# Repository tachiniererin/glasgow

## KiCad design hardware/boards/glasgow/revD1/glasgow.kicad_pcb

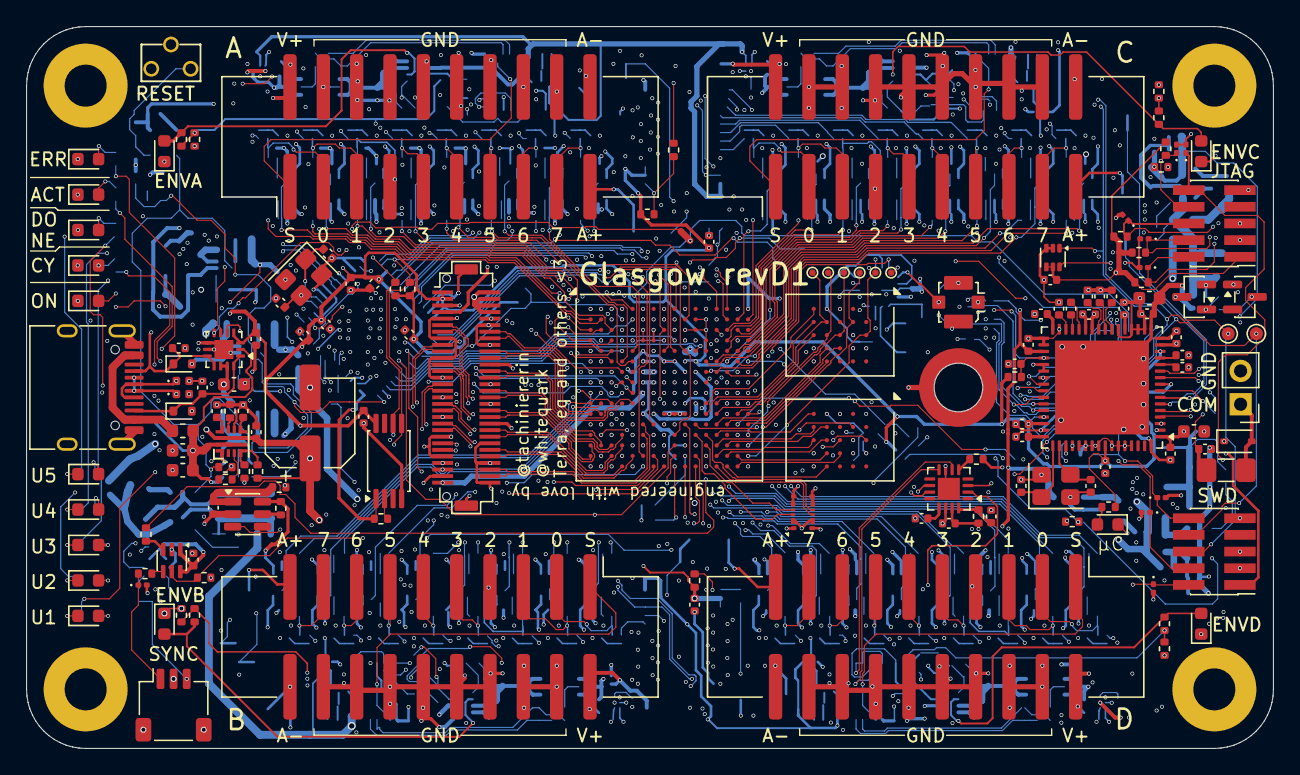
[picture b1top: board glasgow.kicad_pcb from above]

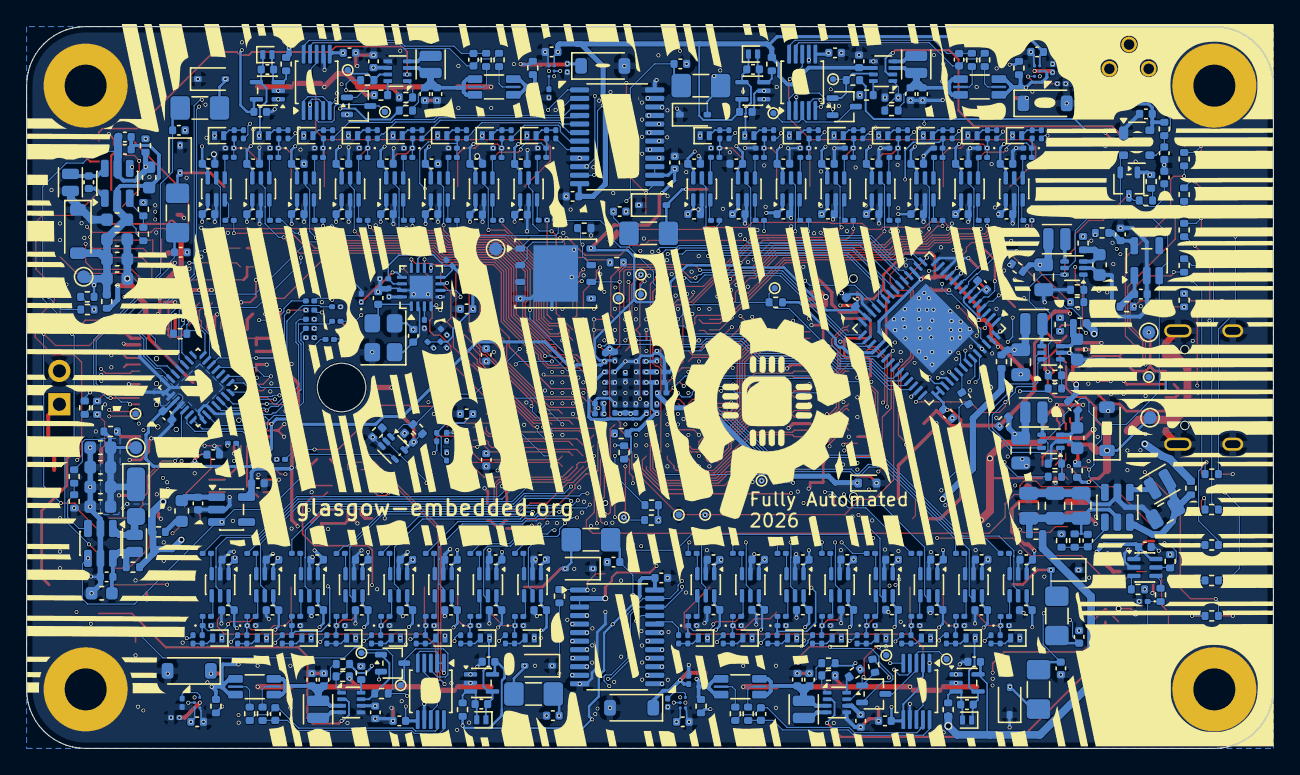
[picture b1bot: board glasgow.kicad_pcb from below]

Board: 6 copper layers, 95.0 x 55.0 mm, 782 parts (626 on the bottom side), 561 nets.

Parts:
C1, C2, C3, C4, C5, C6, C7, C8, C9, C12, C17, C21, C46, C58, C74, C75, C76, C77, C90, C95, C96, C103, C120, C121, C122, C123, C125, C126, C127, C128, C129, C130, C132, C133, C136, C137, C138, C139, C140, C141, C143, C144, C145, C146, C147, C150, C151, C152, C153, C154, C155, C157, C158, C161, C162, C163, C164, C165, C166, C168, C169, C170, C171, C172, C175, C176, C177, C178, C179, C180, C182, C183, C186, C187, C188, C189, C190, C191, C193, C194, C195, C196, C197, C200, C201, C202, C203, C204, C205, C207, C208, C211, C212, C213, C214, C215, C216, C218, C219, C220, C221, C222, C232: 1uF; C_0402_1005Metric
C10, C11, C227, C228: 12pF; C_0402_1005Metric
C13, C18: 470nF; C_0603_1608Metric
C14, C15: 330pF; C_0402_1005Metric
C16, C98, C105, C109, C111, C113, C115: 10uF; C_0603_1608Metric
C19: 4.7nF; C_0402_1005Metric
C20: 1.3nF; C_0402_1005Metric
C22: 220uF; CP_Elec_6.3x4.5
C23, C44, C70, C83, C84, C92, C100, C135, C160, C185, C210, C231: 100nF; C_0402_1005Metric
C24, C26, C27, C29, C31, C32, C45: 4.7uF; C_0402_1005Metric
C25, C28, C33: 1uF/25V; C_0402_1005Metric
C30, C34: 10uF/25V; C_0603_1608Metric
C35: 100pF; C_0402_1005Metric
C36, C38: 10pF; C_0402_1005Metric
C37, C39: 470nF; C_0402_1005Metric
C40, C41, C43: 10nF; C_0402_1005Metric
C42: 1nF/C0G; C_0402_1005Metric
C47, C48, C49, C50, C51, C52, C53, C54, C55: 220pF; C_0402_1005Metric
C56, C57, C59, C60, C61, C62, C63, C64, C65, C66, C67, C68, C69, C72, C73, C78, C79, C116, C117, C118, C119, C224, C225, C226: 1uF; C_0201_0603Metric
C80: 10uF; C_0805_2012Metric
C81, C82, C89: 4.7uF; C_0603_1608Metric
C85, C86, C88, C91, C93, C97: 22uF; C_0805_2012Metric
C87: 360pF; C_0402_1005Metric
C94, C99, C124, C131, C134, C149, C156, C159, C174, C181, C184, C199, C206, C209: 10uF; C_0402_1005Metric
C101, C102, C106: 2.2uF; C_0402_1005Metric
C104: 1.5uF; C_0402_1005Metric
C107: 100nF/50V; C_0402_1005Metric
C108, C110, C112, C114: 10uF/35V; C_0603_1608Metric
C142, C167, C192, C217: 1nF; C_0201_0603Metric
C148, C173, C198, C223: C_0402_1005Metric
D1, D40, D60, D80, D100: GRN; LED_0603_1608Metric
D2, D26: WHT; LED_0603_1608Metric
D3, D24, D28: BLU; LED_0603_1608Metric
D4: ORA; LED_0603_1608Metric
D5: RED; LED_0603_1608Metric
D6, D7: 3.3V; D_0402_1005Metric
D8, D9: 5V; D_SOD-523
D10: 20V; D_SOD-123
D11, D12, D13, D29, D30, D31, D32, D33, D34, D35, D120: 3.3V; D_0201_0603Metric
D14, D25, D27: PNK; LED_0603_1608Metric
D15, D16, D17, D18, D19, D20, D21, D22, D23: 20V; D_SOD-323
D36: 3.6V; D_SOD-523
D37: BAT54AW; SOT-323_SC-70
D38: 30V; D_SOD-123HE
D39: 24V; D_SOD-123
D41, D61, D81, D101: BAT54CW; SOT-323_SC-70
D42, D43, D44, D45, D46, D47, D48, D49, D50, D62, D63, D64, D65, D66, D67, D68, D69, D70, D82, D83, D84, D85, D86, D87, D88, D89, D90, D102, D103, D104, D105, D106, D107, D108, D109, D110: BAT54L; D_SOD-882
D51, D52, D53, D54, D55, D56, D57, D58, D71, D72, D73, D74, D75, D76, D77, D78, D91, D92, D93, D94, D95, D96, D97, D98, D111, D112, D113, D114, D115, D116, D117, D118: 5.5V; D_0201_0603Metric
D59, D79, D99, D119: 6V; D_SOD-123
FB1: 300R/2A; L_0603_1608Metric
FB2: 120R@100MHz; L_0603_1608Metric
G1: Fully_Automated_Logo; fully_automated_logo_silkscreen
H1, H2, H3, H4: MountingHole_Pad; MountingHole_3.2mm_M3_Pad
H5: Addon Mounting Hole; Mounting_Wuerth_WA-SMSI-M2.5_H5mm_9774050151
J1: USB-C; USB_C_Receptacle_HRO_TYPE-C-31-M-12
J2: SWD; PinHeader_2x05_P1.27mm_Vertical_SMD
J3: COM; PinHeader_1x02_P2.54mm_Vertical
J4: SYNC; JST_SH_SM03B-SRSS-TB_1x03-1MP_P1.00mm_Horizontal
J5: JTAG; PinHeader_2x05_P1.27mm_Vertical_SMD
J6: LVDS; Hirose_DF12NB_DF12E3.0-60DP-0.5V_2x30_P0.50mm_Vertical
J7, J8, J9, J10: P1; IDC-Header_2x10_P2.54mm_Vertical_SMD
J11: CLK_EXT; U.FL_Molex_MCRF_73412-0110_Vertical
J12: FPGA_TP; Hirose_BM29_BM29B0.6-4DS_2-0.35V
L1, L7, L8, L9, L10: 2.2uH; L_Changjiang_FTC201612S
L2, L3, L4: 1uH; L_Changjiang_FTC201612S
L5, L6: 10uH; L_Changjiang_FTC201212S
NT1: ACT_BOOT; NetTie-2_SMD_Pad0.5mm
NT2, NT3, NT4, NT5, NT6, NT7, NT8, NT9, NT10, NT11, NT12, NT13, NT14, NT15, NT16, NT17: 0; R_0402_1005Metric
Q1: AO3401; SOT-23
Q2: AO3400; SOT-23
R1, R4, R5: 1.1k; R_0402_1005Metric
R2, R43, R49, R51, R52, R53, R93, R135, R177, R219: 4.7k; R_0402_1005Metric
R3, R7, R8, R9, R41, R45, R47, R273: 2.2k; R_0402_1005Metric
R6: DNP; R_0402_1005Metric
R10, R11, R12, R21, R22, R27, R29, R54, R73, R74, R82, R83, R85, R127, R169, R211, R255, R274: 10k; R_0402_1005Metric
R13, R14, R15, R16, R17, R18, R19, R20, R26: 47; R_0201_0603Metric
R23: 2.87k; R_0402_1005Metric
R24: 280k; R_0402_1005Metric
R25, R71: 120k; R_0402_1005Metric
R28, R42, R44: 13k; R_0402_1005Metric
R30, R31, R32, R33, R34, R35, R36, R37, R38: 2.49k; R_MiniMELF_MMA-0204
R39, R59, R62, R64, R67, R68, R69, R70, R75, R76, R77: 100k; R_0402_1005Metric
R40, R60, R92, R134, R176, R218, R252, R254, R256, R257, R258, R267, R268: 0; R_0402_1005Metric
R46, R50, R58, R272: 100; R_0402_1005Metric
R48, R262, R263, R264, R265: 0; R_0201_0603Metric
R55, R56, R57: 33k; R_0402_1005Metric
R61: 453k; R_0402_1005Metric
R63: 200k; R_0402_1005Metric
R65: 442k; R_0402_1005Metric
R66: 44.2k; R_0402_1005Metric
R72, R89, R91, R131, R133, R173, R175, R215, R217: 4.7; R_0402_1005Metric
R78: 390k; R_0402_1005Metric
R79, R84, R126, R168, R210: 22k; R_0402_1005Metric
R80: 360k; R_0402_1005Metric
R81: 15k; R_0402_1005Metric
R86, R128, R170, R212: 14.3k; R_0402_1005Metric
R87, R129, R171, R213: 68k; R_0402_1005Metric
R88, R130, R172, R214: 24k; R_0402_1005Metric
R90, R132, R174, R216: 50m; R_Shunt_Alt_1206_3216Metric
R94, R95, R96, R97, R98, R99, R100, R101, R102, R103, R104, R105, R106, R107, R108, R109, R136, R137, R138, R139, R140, R141, R142, R143, R144, R145, R146, R147, R148, R149, R150, R151, R178, R179, R180, R181, R182, R183, R184, R185, R186, R187, R188, R189, R190, R191, R192, R193, R220, R221, R222, R223, R224, R225, R226, R227, R228, R229, R230, R231, R232, R233, R234, R235: 100; R_0201_0603Metric
R110, R111, R112, R113, R114, R115, R116, R117, R118, R119, R120, R121, R122, R123, R124, R125, R152, R153, R154, R155, R156, R157, R158, R159, R160, R161, R162, R163, R164, R165, R166, R167, R194, R195, R196, R197, R198, R199, R200, R201, R202, R203, R204, R205, R206, R207, R208, R209, R236, R237, R238, R239, R240, R241, R242, R243, R244, R245, R246, R247, R248, R249, R250, R251, R266: 4.7k; R_0201_0603Metric
R259, R260, R261, R269, R270, R271: 10k; R_0201_0603Metric
SW1: RST; SW_Tactile_SPST_Angled_TC-1109DE
TP1: SDA; TestPoint_Pad_D1.0mm
TP2: SCL; TestPoint_Pad_D1.0mm
TP3: CSSPIN; TestPoint_Pad_D1.0mm
TP5: +15V; TestPoint_Pad_D1.0mm
TP6: -15V; TestPoint_Pad_D1.0mm
TP7: CS#0; TestPoint_Pad_D0.5mm
TP8: CK0; TestPoint_Pad_D0.5mm
TP9: DQS0; TestPoint_Pad_D0.5mm
TP10: DQ0; TestPoint_Pad_D0.5mm
TP11: DQ1; TestPoint_Pad_D0.5mm
TP12: CLKIF; TestPoint_Pad_D0.5mm
TP13: CLKREF; TestPoint_Pad_D0.5mm
TP14: VBUS; TestPoint_Pad_D1.0mm
TP15: CC1; TestPoint_Pad_D1.0mm
TP16: ~{ALERT}; TestPoint_Pad_D0.5mm
TP17, TP18, TP19, TP20: VIO_EN; TestPoint_Pad_D0.5mm
TP21, TP22, TP23, TP24: ~{ALERT}_Vio; TestPoint_Pad_D0.5mm
TP25: FPGA_~{RESET}; TestPoint_Pad_D0.5mm
TP26: FPGA_DONE; TestPoint_Pad_D0.5mm
TP27: FPGA_INITn; TestPoint_Pad_D0.5mm
TP28, TP29, TP30, TP31, TP32: GND; TestPoint_Pad_D0.5mm
U1: BL24C256A-SFRC; TSSOP-8_4.4x3mm_P0.65mm
U2: CY7C68013A-56LTX; QFN-56-1EP_8x8mm_P0.5mm_EP4.5x5.2mm
U3: TMP112xxDRL; SOT-563
U4: FUSB302B01MPX; WQFN-14-1EP_2.5x2.5mm_P0.5mm_EP1.45x1.45mm
U5: TPS259472ARPW; Texas_RPW0010A_VQFN-HR10_2x2x1mm
U6: STM32G031G6Ux; QFN-28_4x4mm_P0.5mm
U7: NAFE71388; VQFN-64-1EP_9x9mm_P0.5mm_EP7.15x7.15mm
U8: LFE5U-25F-8BG256x; BGA-256_14.0x14.0mm_Layout16x16_P0.8mm_Ball0.45mm_Pad0.32mm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
U9: W25Q32JVZP; WSON-8-1EP_6x5mm_P1.27mm_EP3.4x4.3mm
U10, U26, U27, U29, U30, U31, U32, U35, U36, U38, U39, U41, U42, U43, U44, U47, U48, U50, U51, U53, U54, U55, U56, U59, U60, U62, U63, U65, U66, U67, U68, U71, U72, U74: 74AXP1T45; SOT-363_SC-70-6
U11, U12: XccelaOPI; BGA-24_6x8mm_Layout5x5_P1.0mm
U13, U14, U18: TLV62569PDRL; SOT-563
U15: TLV61070ADBV; SOT-23-6
U16: APX811-40UG-7; SOT-143
U17: TLV77525DRL; SOT-23-5
U19: TPS7A2033; SOT-23-5
U20: TPS22917DBV; SOT-23-6
U21: DAC43204; WQFN-16-1EP_3x3mm_P0.5mm_EP1.68x1.68mm
U22: LMR54406; SOT-23-6
U23: SY7208CABC; SOT-23-6
U24, U25: TCA6416APW; TSSOP-24_4.4x7.8mm_P0.65mm
U28, U40, U52, U64: TPS629203; SOT-583-8
U33, U45, U57, U69: NCP456R; WLCSP-6_1.4x1.0mm_P0.4mm
U34, U46, U58, U70: INA233; TSSOP-10_3x3mm_P0.5mm
U37, U49, U61, U73: TLV6001DCK; SOT-353_SC-70-5
U76: 74LVC1G08; SOT-553
Y1: 24M; Crystal_SMD_3225-4Pin_3.2x2.5mm
Y2: 18.432MHz; Crystal_SMD_3225-4Pin_3.2x2.5mm
Y3: Si5351A-B-GM1; QFN-16-1EP_3x3mm_P0.5mm_EP1.75x1.75mm
Y4: 25M; Crystal_SMD_3225-4Pin_3.2x2.5mm

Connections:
+1V1: C59.1, C61.1, C62.1, C64.1, C66.1, C68.1, J6.4, NT13.2, U8.G6 (VCC), U8.G7 (VCC), U8.G9 (VCC), U8.L8 (VCC), U8.L9 (VCC), U8.L10 (VCC)
+1V8: C72.1, C73.1, C74.1, C75.1, C76.1, C77.1, C224.1, C225.1, J6.3, J12.1, J12.5, NT6.2, R260.1, R261.1, R262.2, R264.2, U8.K11 (VCCIO3), U8.L11 (VCCIO3), U11.D1 (V_{CC}), U11.E4 (V_{CC}), U12.D1 (V_{CC}), U12.E4 (V_{CC}), Y3.8 (VDDOB), Y3.11 (VDDOD), Y3.14 (VDDOC)
+2V5: C56.1, C57.1, NT11.2, U8.G11 (VCCAUX), U8.L7 (VCCAUX)
+3V3: C1.1, C2.1, C3.1, C4.1, C5.1, C6.1, C7.1, C8.1, C9.1, C12.1, C17.1, C27.2, C31.1, C32.1, C58.1, C60.1, C63.1, C65.1, C67.1, C69.1, C116.1, C117.1, C118.1, C119.1, C120.1, C121.1, C141.1, C166.1, C191.1, C216.1, C226.2, C232.2, D37.1, J2.1 (VTref), J5.1 (VTref), J6.1, J6.2, NT5.2, NT8.2, NT12.2, R1.1, R6.2, R7.2, R8.2, R9.2, R28.1, R29.1, R49.1, R51.1, R52.1, R53.1, R54.2, R55.1, R56.1, R57.1, R67.1, R82.1, R83.1, R274.1, U1.1 (A0), U1.8 (VCC), U2.3 (AVCC), U2.7 (AVCC), U2.11 (VCC), U2.17 (VCC), U2.27 (VCC), U2.32 (VCC), U2.43 (VCC), U2.44 (WAKEUP), U2.55 (VCC), U3.4 (ADD0), U3.5 (V+), U4.3 (VDD), U4.4 (VDD), U6.3 (VDD), U7.46 (DVDD), U7.57 (DVDD), U8.F6 (VCCIO0), U8.F7 (VCCIO0), U8.F10 (VCCIO1), U8.F11 (VCCIO1), U8.H6 (VCCIO7), U8.H7 (VCCIO7), U8.H11 (VCCIO2), U8.J11 (VCCIO2), U8.L6 (VCCIO8), U9.8 (VCC), U24.2 (VDD_I2C)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
+5V: C16.2, C21.1, C22.1, C84.2, J6.31, J6.32, J6.33, J6.34, NT2.2, NT3.2, NT4.2, NT7.2, NT10.2, NT14.2, NT15.2, R24.1, R59.1, U4.12 (VCONN), U4.13 (VCONN), U5.6 (OUT), U16.4 (VCC)
+5V5: C122.1, C123.1, C124.1, C140.1, C147.1, C149.1, C165.1, C172.1, C174.1, C190.1, C197.1, C199.1, C215.1, C222.1, NT9.2, R93.1, R135.1, R177.1, R219.1, U24.24 (VDD_P), U25.21 (ADDR), U25.24 (VDD_P), U28.6 (VIN), U33.C1 (V_{BIAS}), U37.5 (V+), U40.6 (VIN), U45.C1 (V_{BIAS}), U49.5 (V+), U52.6 (VIN), U57.C1 (V_{BIAS}), U61.5 (V+), U64.6 (VIN), U69.C1 (V_{BIAS}), U73.5 (V+)
+15V: C25.1, C28.1, C30.1, NT16.2, U7.1 (HVDD), U7.15 (HVDD)
-15V: C33.1, C34.1, NT17.1, U7.17 (HVSS), U7.65 (EP)
/A0: U2.37 (PA4/FIOADDR0), U8.D9 (PT40A)
/A1: U2.38 (PA5/FIOADDR1), U8.D8 (PT33B)
/ADC/A1_N: C52.1, R35.1, U7.3 (AI1N)
/ADC/A1_P: C47.1, R30.1, U7.2 (AI1P)
/ADC/A1raw_N: D16.2 (A2), J7.20, R35.2
/ADC/A1raw_P: D15.2 (A2), J7.19, R30.2
/ADC/A2_N: C53.1, R36.1, U7.5 (AI2N)
/ADC/A2_P: C48.1, R31.1, U7.4 (AI2P)
/ADC/A2raw_N: D18.2 (A2), J8.20, R36.2
/ADC/A2raw_P: D17.2 (A2), J8.19, R31.2
/ADC/A3_N: C54.1, R37.1, U7.7 (AI3N)
/ADC/A3_P: C49.1, R32.1, U7.6 (AI3P)
/ADC/A3raw_N: D20.2 (A2), J9.20, R37.2
/ADC/A3raw_P: D19.2 (A2), J9.19, R32.2
/ADC/A4_N: C55.1, R38.1, U7.11 (AI4N)
/ADC/A4_P: C50.1, R33.1, U7.10 (AI4P)
/ADC/A4raw_N: D22.2 (A2), J10.20, R38.2
/ADC/A4raw_P: D21.2 (A2), J10.19, R33.2
/ADC/ADC_~RST: C43.1, R20.2, R29.2, U6.19 (PA10/PA12), U7.36 (~RST)
/ADC/CAPN_ADC: C42.1, U7.29 (CAPN_ADC)
/ADC/CAPP_ADC: C42.2, U7.28 (CAPP_ADC)
/ADC/CIPO: R14.2, U6.12 (SPI1_MISO), U7.44 (SDO)
/ADC/COPI: R15.2, U6.13 (SPI1_MOSI), U7.43 (SDI)
/ADC/DRDY: R13.2, U6.9 (PA3), U7.45 (DRDY)
/ADC/INTB: R19.2, U6.23 (PB3), U7.39 (INTB)
/ADC/MCU_LED: D14.1 (K), U6.7 (PA1)
/ADC/REFH: C41.1, U7.13 (REFH)
/ADC/REFL: C40.1, U7.12 (REFL)
/ADC/REFP_ADC: C46.2, U7.30 (REFP_ADC)
/ADC/REF_BYP: C35.2, U7.23 (REF_BYP)
/ADC/REF_INT: C39.2, U7.25 (REF_INT)
/ADC/REF_NR: C37.2, U7.24 (REF_NR)
/ADC/REMOTE_COM: D23.2 (A2), J3.1, R34.2
/ADC/SCLK: R16.2, U6.11 (SPI1_SCK), U7.42 (SCLK)
/ADC/STM32_NRST: C23.1, D11.1 (K), J2.10 (~RESET), U6.5 (PF2), U76.4
/ADC/SWCLK: D12.1 (K), J2.4 (SWCLK/TCK), R27.2, U6.21 (SYS_SWCLK)
/ADC/SWDIO: D13.1 (K), J2.2 (SWDIO/TMS), U6.20 (SYS_SWDIO)
/ADC/SYNC: R18.2, U6.18 (PA9/PA11), U7.40 (SYNC)
/ADC/~CS: R17.2, U6.16 (PA8), U7.41 (~CS)
/BOOT0: NT1.2, R27.1, U8.E5 (PT13A)
/CIPO: R14.1, U8.B3 (PT4B)
/CLKIF: TP12.1 (1_1), U2.13 (IFCLK), U8.E8 (PCLKT1_1)
/CLKREF: R48.1, TP13.1 (1_1), U2.54 (CLKOUT), U8.C8 (PCLKT1_0)
/COPI: R15.1, U8.A3 (PT6A)
/D0: U2.18 (PB0/FD0), U8.T8 (D0), U9.5 (DI/IO_{0})
/D1: U2.19 (PB1/FD1), U8.T7 (D1), U9.2 (DO/IO_{1})
/D2: U2.20 (PB2/FD2), U8.M7 (D2)
/D3: U2.21 (PB3/FD3), U8.N7 (D3)
/D4: U2.22 (PB4/FD4), U8.P7 (D4)
/D5: U2.23 (PB5/FD5), U8.R7 (D5)
/D6: U2.24 (PB6/FD6), U8.R6 (D6)
/D7: U2.25 (PB7/FD7), U8.T6 (D7)
/DRDY: R13.1, U8.A2 (PT4A)
/ENVA: R10.1, R84.1, R85.1, U2.45 (PD0/FD8)
/ENVB: R11.1, R126.1, R127.1, U2.51 (PD6/FD14)
/ENVC: R12.1, R168.1, R169.1, U2.46 (PD1/FD9)
/ENVD: R21.1, R210.1, R211.1, U2.52 (PD7/FD15)
/FLAGA: R40.2, U2.29 (CTL0/FLAGA), U8.B10 (PT44A)
/FLAGB: U2.30 (CTL1/FLAGB), U8.E10 (PT47B), U8.N9 (CCLK), U9.6 (CLK)
/FLAGC: U2.31 (CTL2/FLAGC), U8.A9 (PT42A)
/FLAGD: U2.40 (PA7/FLAGD/~SLCS), U8.E4 (PT9A)
/FPGA/CLK_3: U8.E7 (GR_PCLK0_1), Y3.12 (CLK3)
/FPGA/CSSPIN: R40.1, TP3.1 (1_1), U8.N8 (BUSY), U9.1 (~CS)
/FPGA/OEB: U8.B6 (PT22B), Y3.6 (OEB)
/FPGA/RAM + LVDS/CK0: TP8.1 (1_1), U8.P16 (PR35A), U11.B2 (CK)
/FPGA/RAM + LVDS/CK1: U8.M11 (PR47A), U12.B2 (CK)
/FPGA/RAM + LVDS/CLK0: U8.L16 (PCLKT3_1), Y3.10 (CLK0)
/FPGA/RAM + LVDS/CLK1: U8.M15 (PCLKC3_0), Y3.7 (CLK1)
/FPGA/RAM + LVDS/CLK2: D120.1 (K), J11.1 (In), Y3.13 (CLK2)
/FPGA/RAM + LVDS/CS#0: TP7.1 (1_1), U8.R16 (PR35B), U11.A3 (CS#)
/FPGA/RAM + LVDS/CS#1: U8.P11 (PR47C), U12.A3 (CS#)
/FPGA/RAM + LVDS/DETECT: J6.35, U8.A5 (PT18A)
/FPGA/RAM + LVDS/DQ0: TP10.1 (1_1), U8.L15 (PR26B), U11.D3 (DQ0)
/FPGA/RAM + LVDS/DQ1: TP11.1 (1_1), U8.K13 (PR29A), U11.D2 (DQ1)
/FPGA/RAM + LVDS/DQ2: U8.M14 (PR32D), U11.C4 (DQ2)
/FPGA/RAM + LVDS/DQ3: U8.M13 (PR35C), U11.D4 (DQ3)
/FPGA/RAM + LVDS/DQ4: U8.M16 (PR26C), U11.D5 (DQ4)
/FPGA/RAM + LVDS/DQ5: U8.L13 (PR29C), U11.E3 (DQ5)
/FPGA/RAM + LVDS/DQ6: U8.L12 (PR29D), U11.E2 (DQ6)
/FPGA/RAM + LVDS/DQ7: U8.K12 (PR29B), U11.E1 (DQ7)
/FPGA/RAM + LVDS/DQ8: U8.R14 (PR41B), U12.D3 (DQ0)
/FPGA/RAM + LVDS/DQ9: U8.P14 (PR38B), U12.D2 (DQ1)
/FPGA/RAM + LVDS/DQ10: U8.T15 (PR38D), U12.C4 (DQ2)
/FPGA/RAM + LVDS/DQ11: U8.R15 (PR38C), U12.D4 (DQ3)
/FPGA/RAM + LVDS/DQ12: U8.T14 (PR41D), U12.D5 (DQ4)
/FPGA/RAM + LVDS/DQ13: U8.R13 (PR41C), U12.E3 (DQ5)
/FPGA/RAM + LVDS/DQ14: U8.P13 (PR41A), U12.E2 (DQ6)
/FPGA/RAM + LVDS/DQ15: U8.N13 (PR38A), U12.E1 (DQ7)
/FPGA/RAM + LVDS/DQS0: TP9.1 (1_1), U8.N16 (PR32A), U11.C3 (DQS/DM0)
/FPGA/RAM + LVDS/DQS1: U8.R12 (PR44A), U12.C3 (DQS/DM0)
/FPGA/RAM + LVDS/N11: J12.2, U8.N11 (PR47B)
/FPGA/RAM + LVDS/N12: J12.7, U8.N12 (PR44D)
/FPGA/RAM + LVDS/P12: J12.3, U8.P12 (PR47D)
/FPGA/RAM + LVDS/T13: J12.6, U8.T13 (PR44B)
/FPGA/RAM + LVDS/VIO_{AUX}: C78.1, C79.1, D36.1 (K), J6.30, U8.J6 (VCCIO6), U8.J7 (VCCIO6)
/FPGA/RAM + LVDS/Z0_N: J6.58, U8.N6 (PL47B)
/FPGA/RAM + LVDS/Z0_P: J6.59, U8.M6 (PL47A)
/FPGA/RAM + LVDS/Z1_N: J6.27, U8.T3 (PL41D)
/FPGA/RAM + LVDS/Z1_P: J6.28, U8.R4 (PL41C)
/FPGA/RAM + LVDS/Z2_N: J6.55, U8.T4 (PL44B)
/FPGA/RAM + LVDS/Z2_P: J6.56, U8.R5 (PL44A)
/FPGA/RAM + LVDS/Z3_N: J6.24, U8.T2 (PL38D)
/FPGA/RAM + LVDS/Z3_P: J6.25, U8.R2 (PL38C)
/FPGA/RAM + LVDS/Z4_N: J6.52, U8.R3 (PL41B)
/FPGA/RAM + LVDS/Z4_P: J6.53, U8.P4 (PL41A)
/FPGA/RAM + LVDS/Z5_N: J6.21, U8.P5 (PL47D)
/FPGA/RAM + LVDS/Z5_P: J6.22, U8.P6 (PL47C)
/FPGA/RAM + LVDS/Z6_N: J6.49, U8.R1 (PL35B)
/FPGA/RAM + LVDS/Z6_P: J6.50, U8.P1 (PL35A)
/FPGA/RAM + LVDS/Z7_N: J6.18, U8.N5 (PL44D)
/FPGA/RAM + LVDS/Z7_P: J6.19, U8.M5 (PL44C)
/FPGA/RAM + LVDS/Z8_N: J6.46, U8.P3 (PL38B)
/FPGA/RAM + LVDS/Z8_P: J6.47, U8.N4 (PL38A)
/FPGA/RAM + LVDS/Z9_N: J6.15, U8.N3 (PL35D)
/FPGA/RAM + LVDS/Z9_P: J6.16, U8.M4 (PL35C)
/FPGA/RAM + LVDS/Z10_N: J6.43, U8.P2 (PL32B)
/FPGA/RAM + LVDS/Z10_P: J6.44, U8.N1 (PL32A)
/FPGA/RAM + LVDS/Z11_N: J6.12, U8.M2 (PL26D)
/FPGA/RAM + LVDS/Z11_P: J6.13, U8.M1 (PL26C)
/FPGA/RAM + LVDS/Z12_N: J6.40, U8.K5 (PL29B)
/FPGA/RAM + LVDS/Z12_P: J6.41, U8.K4 (PL29A)
/FPGA/RAM + LVDS/Z13_N: J6.9, U8.M3 (PL32D)
/FPGA/RAM + LVDS/Z13_P: J6.10, U8.L3 (PL32C)
/FPGA/RAM + LVDS/Z14_N: J6.37, U8.L2 (PL26B)
/FPGA/RAM + LVDS/Z14_P: J6.38, U8.L1 (PL26A)
/FPGA/RAM + LVDS/Z15_N: J6.6, U8.L5 (PL29D)
/FPGA/RAM + LVDS/Z15_P: J6.7, U8.L4 (PL29C)
/FPGA/SYNCBALL: R46.2, U8.B13 (PT60A)
/FPGA/SYNSYN: R58.2, U74.4 (B)
/FPGA/TCK: D30.1 (K), J5.4 (SWCLK/TCK), R49.2, U8.T10 (TCK)
/FPGA/TDI: D34.1 (K), J5.8 (NC/TDI), R53.2, U8.R11 (TDI)
/FPGA/TDO: D33.1 (K), J5.6 (SWO/TDO), R52.2, U8.M10 (TDO)
/FPGA/TMS: D31.1 (K), J5.2 (SWDIO/TMS), R51.2, U8.T11 (TMS)
/FPGA/U1: R41.1, U8.D13 (PT62A)
/FPGA/U2: R42.1, U8.E13 (PT62B)
/FPGA/U3: R43.1, U8.A13 (PT65A)
/FPGA/U4: R44.1, U8.A14 (PT65B)
/FPGA/U5: R45.1, U8.B14 (PT67A)
/FPGA/~SYNC: D32.1 (K), J4.1, R50.1
/FPGA_DONE: R3.1, TP26.1 (1_1), U2.36 (PA3/WU2), U8.P9 (DONE)
/FPGA_INITn: R54.1, TP27.1 (1_1), U6.6 (PA0), U8.T9 (~INIT)
/FPGA_~RESET: D29.1 (K), J5.10 (~RESET), TP25.1 (1_1), U2.34 (PA1/~INT1), U8.R9 (~PROGRAM), U20.3 (ON)
/F_MCU_~RST: R274.2, U8.D5 (PT13B), U76.1
/INTB: R19.1, U8.C4 (PT11A)
/IO Banks/A.DIR0: U8.B1 (PL2A), U26.5 (DIR)
/IO Banks/A.DIR1: U8.C3 (PL2C), U29.5 (DIR)
/IO Banks/A.DIR2: U8.C1 (PL5A), U31.5 (DIR)
/IO Banks/A.DIR3: U8.E3 (PL5C), U35.5 (DIR)
/IO Banks/A.DIR4: U8.D1 (PL8A), U27.5 (DIR)
/IO Banks/A.DIR5: U8.F4 (PL8C), U30.5 (DIR)
/IO Banks/A.DIR6: U8.G5 (PL11A), U32.5 (DIR)
/IO Banks/A.DIR7: U8.F2 (PL11C), U36.5 (DIR)
/IO Banks/A.P0: R118.2, U24.11 (P0_7)
/IO Banks/A.P1: R119.2, U24.10 (P0_6)
/IO Banks/A.P2: R120.2, U24.9 (P0_5)
/IO Banks/A.P3: R121.2, U24.8 (P0_4)
/IO Banks/A.P4: R122.2, U24.7 (P0_3)
/IO Banks/A.P5: R123.2, U24.6 (P0_2)
/IO Banks/A.P6: R124.2, U24.5 (P0_1)
/IO Banks/A.P7: R125.2, U24.4 (P0_0)
/IO Banks/A.Q0: R94.2, U8.B2 (PL2B)
/IO Banks/A.Q1: R95.2, U8.D3 (PL2D)
/IO Banks/A.Q2: R96.2, U8.C2 (PL5B)
/IO Banks/A.Q3: R97.2, U8.F3 (PL5D)
/IO Banks/A.Q4: R98.2, U8.E2 (PL8B)
/IO Banks/A.Q5: R99.2, U8.F5 (PL8D)
/IO Banks/A.Q6: R100.2, U8.G4 (PL11B)
/IO Banks/A.Q7: R101.2, U8.E1 (PL11D)
/IO Banks/B.DIR0: U8.F1 (PL14A), U38.5 (DIR)
/IO Banks/B.DIR1: U8.G3 (PL14C), U41.5 (DIR)
/IO Banks/B.DIR2: U8.H5 (PL17A), U43.5 (DIR)
/IO Banks/B.DIR3: U8.J4 (PL17C), U47.5 (DIR)
/IO Banks/B.DIR4: U8.G1 (PL20A), U39.5 (DIR)
/IO Banks/B.DIR5: U8.J3 (PL20C), U42.5 (DIR)
/IO Banks/B.DIR6: U8.J1 (PL23A), U44.5 (DIR)
/IO Banks/B.DIR7: U8.K1 (PL23C), U48.5 (DIR)
/IO Banks/B.P0: R160.2, U25.20 (P1_7)
/IO Banks/B.P1: R161.2, U25.19 (P1_6)
/IO Banks/B.P2: R162.2, U25.18 (P1_5)
/IO Banks/B.P3: R163.2, U25.17 (P1_4)
/IO Banks/B.P4: R164.2, U25.16 (P1_3)
/IO Banks/B.P5: R165.2, U25.15 (P1_2)
/IO Banks/B.P6: R166.2, U25.14 (P1_1)
/IO Banks/B.P7: R167.2, U25.13 (P1_0)
/IO Banks/B.Q0: R136.2, U8.G2 (PL14B)
/IO Banks/B.Q1: R137.2, U8.H3 (PL14D)
/IO Banks/B.Q2: R138.2, U8.H4 (PL17B)
/IO Banks/B.Q3: R139.2, U8.J5 (PL17D)
/IO Banks/B.Q4: R140.2, U8.H2 (PL20B)
/IO Banks/B.Q5: R141.2, U8.K3 (PL20D)
/IO Banks/B.Q6: R142.2, U8.J2 (PL23B)
/IO Banks/B.Q7: R143.2, U8.K2 (PL23D)
/IO Banks/Bank A/PG: D40.2 (A), R84.2, U28.2 (PG)
/IO Banks/Bank A/VIO_EN: D41.1, R85.2, TP17.1 (1_1), U28.7 (EN)
/IO Banks/Bank A/V_{CLAMP}: C148.1, D42.1 (K), D43.1 (K), D44.1 (K), D45.1 (K), D46.1 (K), D47.1 (K), D48.1 (K), D49.1 (K), D50.1 (K), U37.4
/IO Banks/Bank A/V_{IO_OUT}: D59.1 (K), J7.2, R92.2, R259.1, U33.B2 (OUT)
/IO Banks/Bank A/V_{IO}: C127.1, C128.1, C132.1, C133.1, C138.1, C139.1, C145.1, C146.1, R90.4, R92.1, U26.6 (VCCB), U27.6 (VCCB), U29.6 (VCCB), U30.6 (VCCB), U31.6 (VCCB), U32.6 (VCCB), U33.A1 (EN), U33.B1 (IN), U35.6 (VCCB), U36.6 (VCCB), U37.1 (+)
/IO Banks/Bank A/V_{SENSE}: J7.1, U34.8 (Vbus)
/IO Banks/Bank A/Vin+: C135.1, R89.2, U34.10 (Vin+)
/IO Banks/Bank A/Vin-: C135.2, R91.2, U34.9 (Vin-)
/IO Banks/Bank A/X0: R94.1, U26.3 (A)
/IO Banks/Bank A/X1: R95.1, U29.3 (A)
/IO Banks/Bank A/X2: R96.1, U31.3 (A)
/IO Banks/Bank A/X3: R97.1, U35.3 (A)
/IO Banks/Bank A/X4: R98.1, U27.3 (A)
/IO Banks/Bank A/X5: R99.1, U30.3 (A)
/IO Banks/Bank A/X6: R100.1, U32.3 (A)
/IO Banks/Bank A/X7: R101.1, U36.3 (A)
/IO Banks/Bank A/Y0: R102.1, U26.4 (B)
/IO Banks/Bank A/Y1: R103.1, U29.4 (B)
/IO Banks/Bank A/Y2: R104.1, U31.4 (B)
/IO Banks/Bank A/Y3: R105.1, U35.4 (B)
/IO Banks/Bank A/Y4: R106.1, U27.4 (B)
/IO Banks/Bank A/Y5: R107.1, U30.4 (B)
/IO Banks/Bank A/Y6: R108.1, U32.4 (B)
/IO Banks/Bank A/Y7: R109.1, U36.4 (B)
/IO Banks/Bank A/Z0: D58.1 (K), J7.3, R102.2, R110.1
/IO Banks/Bank A/Z1: D51.1 (K), J7.5, R103.2, R111.1
/IO Banks/Bank A/Z2: D57.1 (K), J7.7, R104.2, R112.1
/IO Banks/Bank A/Z3: D52.1 (K), J7.9, R105.2, R113.1
/IO Banks/Bank A/Z4: D53.1 (K), J7.11, R106.2, R114.1
/IO Banks/Bank A/Z5: D56.1 (K), J7.13, R107.2, R115.1
/IO Banks/Bank A/Z6: D54.1 (K), J7.15, R108.2, R116.1
/IO Banks/Bank A/Z7: D55.1 (K), J7.17, R109.2, R117.1
/IO Banks/Bank B/PG: D60.2 (A), R126.2, U40.2 (PG)
/IO Banks/Bank B/VIO_EN: D61.1, R127.2, TP18.1 (1_1), U40.7 (EN)
/IO Banks/Bank B/V_{CLAMP}: C173.1, D62.1 (K), D63.1 (K), D64.1 (K), D65.1 (K), D66.1 (K), D67.1 (K), D68.1 (K), D69.1 (K), D70.1 (K), U49.4
/IO Banks/Bank B/V_{IO_OUT}: D79.1 (K), J8.2, R134.2, R269.1, U45.B2 (OUT)
/IO Banks/Bank B/V_{IO}: C152.1, C153.1, C157.1, C158.1, C163.1, C164.1, C170.1, C171.1, R132.4, R134.1, U38.6 (VCCB), U39.6 (VCCB), U41.6 (VCCB), U42.6 (VCCB), U43.6 (VCCB), U44.6 (VCCB), U45.A1 (EN), U45.B1 (IN), U47.6 (VCCB), U48.6 (VCCB), U49.1 (+)
/IO Banks/Bank B/V_{SENSE}: J8.1, U46.8 (Vbus)
/IO Banks/Bank B/Vin+: C160.1, R131.2, U46.10 (Vin+)
/IO Banks/Bank B/Vin-: C160.2, R133.2, U46.9 (Vin-)
/IO Banks/Bank B/X0: R136.1, U38.3 (A)
/IO Banks/Bank B/X1: R137.1, U41.3 (A)
/IO Banks/Bank B/X2: R138.1, U43.3 (A)
/IO Banks/Bank B/X3: R139.1, U47.3 (A)
/IO Banks/Bank B/X4: R140.1, U39.3 (A)
/IO Banks/Bank B/X5: R141.1, U42.3 (A)
/IO Banks/Bank B/X6: R142.1, U44.3 (A)
/IO Banks/Bank B/X7: R143.1, U48.3 (A)
/IO Banks/Bank B/Y0: R144.1, U38.4 (B)
/IO Banks/Bank B/Y1: R145.1, U41.4 (B)
/IO Banks/Bank B/Y2: R146.1, U43.4 (B)
/IO Banks/Bank B/Y3: R147.1, U47.4 (B)
/IO Banks/Bank B/Y4: R148.1, U39.4 (B)
/IO Banks/Bank B/Y5: R149.1, U42.4 (B)
/IO Banks/Bank B/Y6: R150.1, U44.4 (B)
/IO Banks/Bank B/Y7: R151.1, U48.4 (B)
/IO Banks/Bank B/Z0: D78.1 (K), J8.3, R144.2, R152.1
/IO Banks/Bank B/Z1: D71.1 (K), J8.5, R145.2, R153.1
/IO Banks/Bank B/Z2: D77.1 (K), J8.7, R146.2, R154.1
/IO Banks/Bank B/Z3: D72.1 (K), J8.9, R147.2, R155.1
/IO Banks/Bank B/Z4: D73.1 (K), J8.11, R148.2, R156.1
/IO Banks/Bank B/Z5: D76.1 (K), J8.13, R149.2, R157.1
/IO Banks/Bank B/Z6: D74.1 (K), J8.15, R150.2, R158.1
/IO Banks/Bank B/Z7: D75.1 (K), J8.17, R151.2, R159.1
/IO Banks/Bank C/PG: D80.2 (A), R168.2, U52.2 (PG)
/IO Banks/Bank C/VIO_EN: D81.1, R169.2, TP19.1 (1_1), U52.7 (EN)
/IO Banks/Bank C/V_{CLAMP}: C198.1, D82.1 (K), D83.1 (K), D84.1 (K), D85.1 (K), D86.1 (K), D87.1 (K), D88.1 (K), D89.1 (K), D90.1 (K), U61.4
/IO Banks/Bank C/V_{IO_OUT}: D99.1 (K), J9.2, R176.2, R270.1, U57.B2 (OUT)
/IO Banks/Bank C/V_{IO}: C177.1, C178.1, C182.1, C183.1, C188.1, C189.1, C195.1, C196.1, R174.4, R176.1, U50.6 (VCCB), U51.6 (VCCB), U53.6 (VCCB), U54.6 (VCCB), U55.6 (VCCB), U56.6 (VCCB), U57.A1 (EN), U57.B1 (IN), U59.6 (VCCB), U60.6 (VCCB), U61.1 (+)
/IO Banks/Bank C/V_{SENSE}: J9.1, U58.8 (Vbus)
/IO Banks/Bank C/Vin+: C185.1, R173.2, U58.10 (Vin+)
/IO Banks/Bank C/Vin-: C185.2, R175.2, U58.9 (Vin-)
/IO Banks/Bank C/X0: R178.1, U50.3 (A)
/IO Banks/Bank C/X1: R179.1, U53.3 (A)
/IO Banks/Bank C/X2: R180.1, U55.3 (A)
/IO Banks/Bank C/X3: R181.1, U59.3 (A)
/IO Banks/Bank C/X4: R182.1, U51.3 (A)
/IO Banks/Bank C/X5: R183.1, U54.3 (A)
/IO Banks/Bank C/X6: R184.1, U56.3 (A)
/IO Banks/Bank C/X7: R185.1, U60.3 (A)
/IO Banks/Bank C/Y0: R186.1, U50.4 (B)
/IO Banks/Bank C/Y1: R187.1, U53.4 (B)
/IO Banks/Bank C/Y2: R188.1, U55.4 (B)
/IO Banks/Bank C/Y3: R189.1, U59.4 (B)
/IO Banks/Bank C/Y4: R190.1, U51.4 (B)
/IO Banks/Bank C/Y5: R191.1, U54.4 (B)
/IO Banks/Bank C/Y6: R192.1, U56.4 (B)
/IO Banks/Bank C/Y7: R193.1, U60.4 (B)
/IO Banks/Bank C/Z0: D98.1 (K), J9.3, R186.2, R194.1
/IO Banks/Bank C/Z1: D91.1 (K), J9.5, R187.2, R195.1
/IO Banks/Bank C/Z2: D97.1 (K), J9.7, R188.2, R196.1
/IO Banks/Bank C/Z3: D92.1 (K), J9.9, R189.2, R197.1
/IO Banks/Bank C/Z4: D93.1 (K), J9.11, R190.2, R198.1
/IO Banks/Bank C/Z5: D96.1 (K), J9.13, R191.2, R199.1
/IO Banks/Bank C/Z6: D94.1 (K), J9.15, R192.2, R200.1
/IO Banks/Bank C/Z7: D95.1 (K), J9.17, R193.2, R201.1
/IO Banks/Bank D/PG: D100.2 (A), R210.2, U64.2 (PG)
/IO Banks/Bank D/VIO_EN: D101.1, R211.2, TP20.1 (1_1), U64.7 (EN)
/IO Banks/Bank D/V_{CLAMP}: C223.1, D102.1 (K), D103.1 (K), D104.1 (K), D105.1 (K), D106.1 (K), D107.1 (K), D108.1 (K), D109.1 (K), D110.1 (K), U73.4
/IO Banks/Bank D/V_{IO_OUT}: D119.1 (K), J10.2, R218.2, R271.1, U69.B2 (OUT)
/IO Banks/Bank D/V_{IO}: C202.1, C203.1, C207.1, C208.1, C213.1, C214.1, C220.1, C221.1, R216.4, R218.1, U62.6 (VCCB), U63.6 (VCCB), U65.6 (VCCB), U66.6 (VCCB), U67.6 (VCCB), U68.6 (VCCB), U69.A1 (EN), U69.B1 (IN), U71.6 (VCCB), U72.6 (VCCB), U73.1 (+)
/IO Banks/Bank D/V_{SENSE}: J10.1, U70.8 (Vbus)
/IO Banks/Bank D/Vin+: C210.1, R215.2, U70.10 (Vin+)
/IO Banks/Bank D/Vin-: C210.2, R217.2, U70.9 (Vin-)
/IO Banks/Bank D/X0: R220.1, U62.3 (A)
/IO Banks/Bank D/X1: R221.1, U65.3 (A)
/IO Banks/Bank D/X2: R222.1, U67.3 (A)
/IO Banks/Bank D/X3: R223.1, U71.3 (A)
/IO Banks/Bank D/X4: R224.1, U63.3 (A)
/IO Banks/Bank D/X5: R225.1, U66.3 (A)
/IO Banks/Bank D/X6: R226.1, U68.3 (A)
/IO Banks/Bank D/X7: R227.1, U72.3 (A)
/IO Banks/Bank D/Y0: R228.1, U62.4 (B)
/IO Banks/Bank D/Y1: R229.1, U65.4 (B)
/IO Banks/Bank D/Y2: R230.1, U67.4 (B)
/IO Banks/Bank D/Y3: R231.1, U71.4 (B)
/IO Banks/Bank D/Y4: R232.1, U63.4 (B)
/IO Banks/Bank D/Y5: R233.1, U66.4 (B)
/IO Banks/Bank D/Y6: R234.1, U68.4 (B)
/IO Banks/Bank D/Y7: R235.1, U72.4 (B)
/IO Banks/Bank D/Z0: D118.1 (K), J10.3, R228.2, R236.1
/IO Banks/Bank D/Z1: D111.1 (K), J10.5, R229.2, R237.1
/IO Banks/Bank D/Z2: D117.1 (K), J10.7, R230.2, R238.1
/IO Banks/Bank D/Z3: D112.1 (K), J10.9, R231.2, R239.1
/IO Banks/Bank D/Z4: D113.1 (K), J10.11, R232.2, R240.1
/IO Banks/Bank D/Z5: D116.1 (K), J10.13, R233.2, R241.1
/IO Banks/Bank D/Z6: D114.1 (K), J10.15, R234.2, R242.1
/IO Banks/Bank D/Z7: D115.1 (K), J10.17, R235.2, R243.1
/IO Banks/C.DIR0: U8.B15 (PR2B), U50.5 (DIR)
/IO Banks/C.DIR1: U8.D14 (PR2D), U53.5 (DIR)
/IO Banks/C.DIR2: U8.C15 (PR5B), U55.5 (DIR)
/IO Banks/C.DIR3: U8.F14 (PR5D), U59.5 (DIR)
/IO Banks/C.DIR4: U8.E15 (PR8B), U51.5 (DIR)
/IO Banks/C.DIR5: U8.F12 (PR8D), U54.5 (DIR)
/IO Banks/C.DIR6: U8.G13 (PR11B), U56.5 (DIR)
/IO Banks/C.DIR7: U8.E16 (PR11D), U60.5 (DIR)
/IO Banks/C.P0: R202.2, U24.20 (P1_7)
/IO Banks/C.P1: R203.2, U24.19 (P1_6)
/IO Banks/C.P2: R204.2, U24.18 (P1_5)
/IO Banks/C.P3: R205.2, U24.17 (P1_4)
/IO Banks/C.P4: R206.2, U24.16 (P1_3)
/IO Banks/C.P5: R207.2, U24.15 (P1_2)
/IO Banks/C.P6: R208.2, U24.14 (P1_1)
/IO Banks/C.P7: R209.2, U24.13 (P1_0)
/IO Banks/C.Q0: R178.2, U8.B16 (PR2A)
/IO Banks/C.Q1: R179.2, U8.C14 (PR2C)
/IO Banks/C.Q2: R180.2, U8.C16 (PR5A)
/IO Banks/C.Q3: R181.2, U8.E14 (PR5C)
/IO Banks/C.Q4: R182.2, U8.D16 (PR8A)
/IO Banks/C.Q5: R183.2, U8.F13 (PR8C)
/IO Banks/C.Q6: R184.2, U8.G12 (PR11A)
/IO Banks/C.Q7: R185.2, U8.F15 (PR11C)
/IO Banks/D.DIR0: U8.G15 (PR14B), U62.5 (DIR)
/IO Banks/D.DIR1: U8.H14 (PR14D), U65.5 (DIR)
/IO Banks/D.DIR2: U8.H13 (PR17B), U67.5 (DIR)
/IO Banks/D.DIR3: U8.J12 (PR17D), U71.5 (DIR)
/IO Banks/D.DIR4: U8.H15 (PR20B), U63.5 (DIR)
/IO Banks/D.DIR5: U8.K14 (PR20D), U66.5 (DIR)
/IO Banks/D.DIR6: U8.J15 (PR23B), U68.5 (DIR)
/IO Banks/D.DIR7: U8.K15 (PR23D), U72.5 (DIR)
/IO Banks/D.P0: R244.2, U25.11 (P0_7)
/IO Banks/D.P1: R245.2, U25.10 (P0_6)
/IO Banks/D.P2: R246.2, U25.9 (P0_5)
/IO Banks/D.P3: R247.2, U25.8 (P0_4)
/IO Banks/D.P4: R248.2, U25.7 (P0_3)
/IO Banks/D.P5: R249.2, U25.6 (P0_2)
/IO Banks/D.P6: R250.2, U25.5 (P0_1)
/IO Banks/D.P7: R251.2, U25.4 (P0_0)
/IO Banks/D.Q0: R220.2, U8.F16 (PR14A)
/IO Banks/D.Q1: R221.2, U8.G14 (PR14C)
/IO Banks/D.Q2: R222.2, U8.H12 (PR17A)
/IO Banks/D.Q3: R223.2, U8.J13 (PR17C)
/IO Banks/D.Q4: R224.2, U8.G16 (PR20A)
/IO Banks/D.Q5: R225.2, U8.J14 (PR20C)
/IO Banks/D.Q6: R226.2, U8.J16 (PR23A)
/IO Banks/D.Q7: R227.2, U8.K16 (PR23C)
/IO Banks/V_{SET_A}: R87.2, R88.1, U21.11 (OUT0), U28.1 (FB)
/IO Banks/V_{SET_B}: R129.2, R130.1, U21.10 (OUT1), U40.1 (FB)
/IO Banks/V_{SET_C}: R171.2, R172.1, U21.3 (OUT2), U52.1 (FB)
/IO Banks/V_{SET_D}: R213.2, R214.1, U21.2 (OUT3), U64.1 (FB)
/LED_ACT: R4.1, U2.49 (PD4/FD12)
/LED_CY: NT1.1, R2.1, U2.47 (PD2/FD10)
/LED_ERR: R5.1, U2.50 (PD5/FD13)
/MCU_~RST: R254.1, R255.1, U76.2
/NAFE_CLK_{OUT}: R26.2, R48.2
/NAFE_{~CS}: R17.1, U8.C9 (PT38B)
/NAFE_{~RST}: R20.1, U8.A15 (PT67B)
/OE: U2.35 (PA2/SLOE), U8.B5 (PT15B)
/PG_{VBUS}: C83.1, R59.2, R60.1, R252.2, SW1.2, U16.3 (~MR)
/PKTEND: U2.39 (PA6/PKTEND), U8.E11 (PT51B)
/Power/1V1OUT: C97.1, L4.2, NT13.1, R70.1
/Power/1V8OUT: C86.1, L3.2, NT6.1, R63.1
/Power/2V5OUT: C94.1, NT11.1, U17.5 (OUT)
/Power/3V3LSIN: C95.1, NT12.1, U20.1 (VIN)
/Power/3V3OUT: C85.1, L2.2, NT5.1, R61.1
/Power/5V5OUT: C87.1, C88.1, C91.1, C93.1, NT9.1, R65.1, U15.5 (V_{OUT})
/Power/BO5V5IN: C80.1, L1.1, NT2.1, U15.6 (V_{IN})
/Power/BOIN: C105.1, C106.1, L5.1, NT15.1, U23.6 (IN)
/Power/BOOST_OUT15V: C109.1, C111.1, C113.1, C115.1, D38.1 (K), NT16.1, R80.1, TP5.1 (1_1)
/Power/BU1V1IN: C89.1, NT7.1, U18.3 (VIN)
/Power/BU1V8IN: C82.1, NT4.1, U14.3 (VIN)
/Power/BU3V3IN: C81.1, NT3.1, U13.3 (VIN)
/Power/EN: Q2.3 (D), R76.2, U22.4 (EN)
/Power/IBBIN: C98.1, C101.1, C102.1, NT14.1, Q1.2 (S), R76.1, U22.5 (IN)
/Power/INVBUBO_LOCALGND: C98.2, C101.2, C102.2, C108.2, C110.2, C112.2, C114.2, D39.2 (A), NT17.2, Q2.2 (S), R77.1, R79.2, TP6.1 (1_1), U22.2 (GND)
/Power/LDOVDDAIN: FB2.1, NT10.1
/Power/U1FB: R80.2, R81.1, U23.3 (FB)
/Power/U1SW: D38.2 (A), L5.2, U23.1 (SW)
/Power/U2FB: R78.2, R79.1, U22.3 (FB)
/Power/U2SW: C107.2, L6.1, U22.6 (SW)
/Power/VAUXLDOIN: C90.1, NT8.1, U17.1 (IN)
/RD: U2.1 (RDY0/SLRD), U8.E9 (PT40B)
/SCL: J2.6 (SWO/TDO), R8.1, TP2.1 (1_1), U1.6 (SCL), U2.15 (SCL), U3.1 (SCL), U4.6 (SCL), U6.26 (PB6), U8.A12 (PT53B), U21.6 (SCL/~SYNC), U24.22 (SCL), U25.22 (SCL), U34.1 (A1), U34.5 (SCL), U46.1 (A1), U46.5 (SCL), U58.1 (A1), U58.5 (SCL), U70.1 (A1), U70.2 (A0), U70.5 (SCL), Y3.4 (SCL)
/SCLK: R16.1, U8.A8 (PT29B)
/SDA: J2.8 (NC/TDI), R7.1, TP1.1 (1_1), U1.5 (SDA), U2.16 (SDA), U3.6 (SDA), U4.7 (SDA), U6.27 (PB7), U8.D11 (PT51A), U21.8 (SDA/SCLK), U24.23 (SDA), U25.23 (SDA), U34.4 (SDA), U46.4 (SDA), U58.2 (A0), U58.4 (SDA), U70.4 (SDA), Y3.5 (SDA)
/SYNC: R18.1, U8.D4 (PT9B)
/USB/CC1: C14.1, D8.1 (K), J1.A5 (CC1), TP15.1 (1_1), U4.10 (CC1), U4.11 (CC1)
/USB/CC2: C15.1, D9.1 (K), J1.B5 (CC2), U4.1 (CC2), U4.14 (CC2)
/USB/VBUS: C13.2, C18.2, D10.1 (K), FB1.2, R22.2, TP14.1 (1_1), U4.2 (VBUS), U5.5 (IN)
/USB/xVBUS: FB1.1, J1.A4 (VBUS), J1.A9 (VBUS), J1.B4 (VBUS), J1.B9 (VBUS)
/USB_N: D7.1 (K), J1.A7 (D-), J1.B7 (D-), U2.9 (D-)
/USB_P: D6.1 (K), J1.A6 (D+), J1.B6 (D+), U2.8 (D+)
/WR: U2.2 (RDY1/SLWR), U8.D10 (PT47A)
/XTALIN: C11.2, U2.5 (XTALIN), Y1.1
/XTALOUT: C10.2, U2.4 (XTALOUT), Y1.3
/~ALERT: D41.2, D61.2, D81.2, D101.2, R9.1, R257.2, R258.1, R268.2, TP16.1 (1_1), U2.33 (PA0/~INT0), U6.25 (I2C1_SMBA), U8.B4 (PT11B)
/~CY_RESET: C92.1, D37.3, R68.2, U2.42 (~RESET), U13.6 (PG), U14.6 (PG), U18.6 (PG)
CFG0: R55.2, U6.14 (PB0), U8.N10 (CFG_0)
CFG2: R57.2, U6.15 (PB1), U8.R10 (CFG_2)
FLASH_~HOLD: R39.2, U6.24 (PB4), U9.7 (~HOLD/~RESET/IO_{3})
GND: C1.2, C2.2, C3.2, C4.2, C5.2, C6.2, C7.2, C8.2, C9.2, C10.1, C11.1, C12.2, C13.1, C14.2, C15.2, C16.1, C17.2, C18.1, C19.1, C20.1, C21.2, C22.2, C23.2, C24.2, C25.2, C26.2, C27.1, C28.2, C29.2, C30.2, C31.2, C32.2, C33.2, C34.2, C35.1, C36.2, C37.1, C38.2, C39.1, C40.2, C41.2, C43.2, C44.2, C45.2, C46.1, C47.2, C48.2, C49.2, C50.2, C51.2, C52.2, C53.2, C54.2, C55.2, C56.2, C57.2, C58.2, C59.2, C60.2, C61.2, C62.2, C63.2, C64.2, C65.2, C66.2, C67.2, C68.2, C69.2, C70.1, C72.2, C73.2, C74.2, C75.2, C76.2, C77.2, C78.2, C79.2, C80.2, C81.2, C82.2, C83.2, C84.1, C85.2, C86.2, C88.2, C89.2, C90.2, C91.2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
LS_3V3: C70.2, C125.2, C126.2, C129.2, C130.2, C136.2, C137.2, C143.2, C144.2, C150.2, C151.2, C154.2, C155.2, C161.2, C162.2, C168.2, C169.2, C175.2, C176.2, C179.2, C180.2, C186.2, C187.2, C193.2, C194.2, C200.2, C201.2, C204.2, C205.2, C211.2, C212.2, C218.2, C219.2, C231.1, R72.2, U10.1 (VCCA), U10.6 (VCCB), U20.6 (VOUT), U26.1 (VCCA), U27.1 (VCCA), U29.1 (VCCA), U30.1 (VCCA), U31.1 (VCCA), U32.1 (VCCA), U35.1 (VCCA), U36.1 (VCCA), U38.1 (VCCA), U39.1 (VCCA), U41.1 (VCCA), U42.1 (VCCA), U43.1 (VCCA), U44.1 (VCCA), U47.1 (VCCA), U48.1 (VCCA), U50.1 (VCCA), U51.1 (VCCA), U53.1 (VCCA), U54.1 (VCCA), U55.1 (VCCA), U56.1 (VCCA), U59.1 (VCCA), U60.1 (VCCA), U62.1 (VCCA), U63.1 (VCCA), U65.1 (VCCA), U66.1 (VCCA), U67.1 (VCCA), U68.1 (VCCA), U71.1 (VCCA), U72.1 (VCCA), U74.1 (VCCA), U74.6 (VCCB)
unnamed: C51.1, R34.1, R267.2
unnamed: D1.2 (A), R1.2
unnamed: D2.2 (A), R2.2
unnamed: D3.2 (A), R3.2
unnamed: D4.2 (A), R4.2
unnamed: D5.2 (A), R5.2
unnamed: D14.2 (A), R28.2
unnamed: D24.2 (A), R41.2
unnamed: D25.2 (A), R42.2
unnamed: D26.2 (A), R43.2
unnamed: D27.2 (A), R44.2
unnamed: D28.2 (A), R45.2
unnamed: D35.1 (K), J4.3, R58.1
unnamed: C148.2, D42.2 (A), R93.2, U37.3 (-)
unnamed: D43.2 (A), R110.2, R118.1
unnamed: D44.2 (A), R111.2, R119.1
unnamed: D45.2 (A), R112.2, R120.1
unnamed: D46.2 (A), R113.2, R121.1
unnamed: D47.2 (A), R114.2, R122.1
unnamed: D48.2 (A), R115.2, R123.1
unnamed: D49.2 (A), R116.2, R124.1
unnamed: D50.2 (A), R117.2, R125.1
unnamed: C173.2, D62.2 (A), R135.2, U49.3 (-)
unnamed: D63.2 (A), R152.2, R160.1
unnamed: D64.2 (A), R153.2, R161.1
unnamed: D65.2 (A), R154.2, R162.1
unnamed: D66.2 (A), R155.2, R163.1
unnamed: D67.2 (A), R156.2, R164.1
unnamed: D68.2 (A), R157.2, R165.1
unnamed: D69.2 (A), R158.2, R166.1
unnamed: D70.2 (A), R159.2, R167.1
unnamed: C198.2, D82.2 (A), R177.2, U61.3 (-)
unnamed: D83.2 (A), R194.2, R202.1
unnamed: D84.2 (A), R195.2, R203.1
unnamed: D85.2 (A), R196.2, R204.1
unnamed: D86.2 (A), R197.2, R205.1
unnamed: D87.2 (A), R198.2, R206.1
unnamed: D88.2 (A), R199.2, R207.1
unnamed: D89.2 (A), R200.2, R208.1
unnamed: D90.2 (A), R201.2, R209.1
unnamed: C223.2, D102.2 (A), R219.2, U73.3 (-)
unnamed: D103.2 (A), R236.2, R244.1
unnamed: D104.2 (A), R237.2, R245.1
unnamed: D105.2 (A), R238.2, R246.1
unnamed: D106.2 (A), R239.2, R247.1
unnamed: D107.2 (A), R240.2, R248.1
unnamed: D108.2 (A), R241.2, R249.1
unnamed: D109.2 (A), R242.2, R250.1
unnamed: D110.2 (A), R243.2, R251.1
unnamed: Q1.3 (D), R75.1
unnamed: D37.2, Q1.1 (G), R60.2, R69.2, U13.5 (EN), U14.5 (EN), U15.3 (EN), U16.2 (~RESET), U17.3 (EN), U18.5 (EN), U19.3 (EN), U23.4 (EN)
unnamed: Q2.1 (G), R75.2, R77.2
unnamed: R67.2, R68.1
unnamed: R89.1, R90.2
unnamed: R90.3, R91.1
unnamed: R131.1, R132.2
unnamed: R132.3, R133.1
unnamed: R173.1, R174.2
unnamed: R174.3, R175.1
unnamed: R215.1, R216.2
unnamed: R216.3, R217.1
unnamed: R260.2, U11.A4
unnamed: R261.2, U12.A4
unnamed: R262.1, U12.B4
unnamed: R263.1, U12.B3
unnamed: R264.1, U11.B4
unnamed: R265.1, U11.B3
unnamed: R6.1, U1.2 (A1)
unnamed: R254.2, U2.48 (PD3/FD11)
unnamed: R257.1, U4.5 (INT_N)
unnamed: C19.2, U5.7 (DVDT)
unnamed: R22.1, U5.1 (EN)
unnamed: R23.1, U5.9 (ILM)
unnamed: C20.2, U5.10 (ITIMER)
unnamed: R252.1, U5.3 (PG)
unnamed: R24.2, R25.1, U5.4 (PGTH)
unnamed: R256.1, R267.1, U7.8 (AICOM)
unnamed: C38.1, U7.50 (EXTCLK/XI), Y2.3
unnamed: R26.1, U7.52 (GPIO9)
unnamed: C45.1, U7.48 (LDO_DIG)
unnamed: C44.1, U7.32 (REF_EXT)
unnamed: C36.1, U7.49 (XO), Y2.1
unnamed: R272.2, U8.M8 (PB15B)
unnamed: R56.2, U8.P10 (CFG_1)
unnamed: R46.1, U10.3 (A)
unnamed: R50.2, U10.4 (B)
unnamed: R47.1, U8.C13 (PT60B), U10.5 (DIR)
unnamed: R61.2, R62.1, U13.1 (FB)
unnamed: L2.1, U13.4 (SW)
unnamed: R63.2, R64.1, U14.1 (FB)
unnamed: L3.1, U14.4 (SW)
unnamed: L1.2, U15.1 (SW)
unnamed: C87.2, R65.2, R66.1, U15.4 (V_{FB})
unnamed: R70.2, R71.1, U18.1 (FB)
unnamed: L4.1, U18.4 (SW)
unnamed: C96.1, FB2.2, U19.1 (VIN)
unnamed: R72.1, U20.5 (QOD)
unnamed: C104.1, U21.13 (CAP)
unnamed: R74.1, U21.5 (GPIO/SDO)
unnamed: C100.2, R73.2, U21.16 (VREF)
unnamed: C107.1, U22.1 (BS)
unnamed: R82.2, R258.2, U24.1 (~INT)
unnamed: R83.2, R268.1, U25.1 (~INT)
unnamed: R86.1, U28.8 (S-CONF)
unnamed: L7.1, U28.4 (SW)
unnamed: C131.1, C134.1, L7.2, R87.1, R90.1, U28.3 (VOS)
unnamed: C142.1, U33.A2 (Gate)
unnamed: D41.3, TP21.1 (1_1), U34.3 (~Alert)
unnamed: R128.1, U40.8 (S-CONF)
unnamed: L8.1, U40.4 (SW)
unnamed: C156.1, C159.1, L8.2, R129.1, R132.1, U40.3 (VOS)
unnamed: C167.1, U45.A2 (Gate)
unnamed: D61.3, TP22.1 (1_1), U46.3 (~Alert)
unnamed: R170.1, U52.8 (S-CONF)
unnamed: L9.1, U52.4 (SW)
unnamed: C181.1, C184.1, L9.2, R171.1, R174.1, U52.3 (VOS)
unnamed: C192.1, U57.A2 (Gate)
unnamed: D81.3, TP23.1 (1_1), U58.3 (~Alert)
unnamed: R212.1, U64.8 (S-CONF)
unnamed: L10.1, U64.4 (SW)
unnamed: C206.1, C209.1, L10.2, R213.1, R216.1, U64.3 (VOS)
unnamed: C217.1, U69.A2 (Gate)
unnamed: D101.3, TP24.1 (1_1), U70.3 (~Alert)
unnamed: R272.1, U74.3 (A)
unnamed: R273.1, U8.M9 (PB18A), U74.5 (DIR)
unnamed: R266.2, Y3.3 (A0)
unnamed: C227.2, Y3.1 (XA), Y4.3
unnamed: C228.2, Y3.2 (XB), Y4.1
VDDA: C24.1, C26.1, C29.1, C99.1, C103.1, R73.1, U7.21 (AVDD), U7.26 (AVDD), U7.35 (AVDD), U19.5 (VOUT), U21.15 (VDD)

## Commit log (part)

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2026-06-09 wip rev_d pin mapping
